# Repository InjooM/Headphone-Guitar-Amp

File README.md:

# Headphone-Guitar-Amp
## Preface
Electric guitar amplifier
I've been meaning to work on my Github more, and I thought this personal project would be the perfect addition to my portfolio. I found a schematic online for a Class AB audio amplifier, and I'm trying my best to follow a procedure where I can ensure the ability to diagnose and treat each and every problem that occurs within my design.

## Finding the circuit
First, I found an [amplifier circuit](http://www.generalguitargadgets.com/pdf/ggg_mxr_hpamp_sc.pdf), and drew it out to help me understand and analyze it. Then I simulated it in Multisim to confirm my calculations. I've included the simulation files in this project.

## Prototyping
I ordered parts and assembled everything onto a protoboard. The amplifier worked properly. I've worked on projects in the past where I'd skip this step, in faith of the circuit I found working out-of-the-box. However, I think this is bad practice, and this step is a good redudancy in case something needs to be tweaked before a board is designed.
Here are some pictures I took of the breadboard. 

## Designing the board
I found footprints off of Mouser for the parts I ordered, then created a schematic in Eagle. After running an ERC, and manually double checking each section of the circuit, I moved over to the board. The board design was quite simple. I tried to keep all capacitors close to I/O, and managed to squeeze all the components into a 40 mm x 70 mm board. I ordered 3 copies of this board from OshPark. I've included the board's files in this project.

## Designing the case
I've worked with Autodesk Fusion and Inventor so I decided to make a casing for this project too. Nothing too special: just a box with faces I can glue together. After a few iterations, it came out fine. I used a friends Creality CR-10 to print. A few issues I ran into were small things: forgetting to add indents to mount connectors and a few errors with Creality's splicer. This cost me some time, and I really should slow down when working on prints. I tend to look over these small mistakes, and it ends up wasting some material. Looking back, I would've also like to add a hinge somewhere inside the top lid to keep things accessible, but besides that the case does the job well. All the dimensions came out correctly, and everything fit within a millimeter or two. I've included the STL's in this project.

## Assembly
Finally, after the boards and parts came in and the prints were finished, I assembled everything. I was nervous about this part, since I didn't have a testbench at home to debug the board if anything went wrong. I only had a multimeter, and I was prepared to use the probes on the via's of the board in case something was wrong. Thankfully, everything worked as soon as it all came together. It sounds better than when I was prototyping it, perhaps due to capcitance in the breadboard? It has a very-small form factor, fits in my palm, and I'm happy about how it turned out.
Here are some screenshots of the finished product.

## Final Thoughts
I initially started this project to save some money on an amp, and to keep my hands busy. If I were to go back and restart the project, I'd definitely make a few changes. For one, I'd find a little more developed circuit, or perhaps a better quality op-amp. I'm not well-versed in the market of op-amps, but I'm sure if I used something better than a general 741, I would get a little less noise from the amp. I also wouldn't have used EAGLE. EAGLE's package system is useful when working on large organized projects, but for something as small as this board, I probably could've used gEDA PCB and spent less time downloading or designing footprints for each component. I also would've chose JLC PCB instead of OSHPark, since although OSHPark makes great boards, it was a lot more expensive. For the casing, I would've wanted the hinge like I mentioned in the above section, and maybe standoffs for the board. As of now, it's just glued to the base plastic piece, which is a little lackluster, and potentially could cause some problems if the plastic or glue ends up being conductive. I also would've liked smoother edges on the casing. The corners are a little sharp.

Otherwise, I'm proud of how this turned out. This was a small pet project I wanted to do on the side to keep me busy while I'm taking classes. I got to use techniques I've learned in school that I haven't used yet for other projects, which was really fun. Analyzing my circuit using the methods I've learned in classes, and seeing it work as I thought in Multisim was very cool. I'm already thinking of new iterations with wireless functionality, so maybe a bluetooth device/interface will be my next project.

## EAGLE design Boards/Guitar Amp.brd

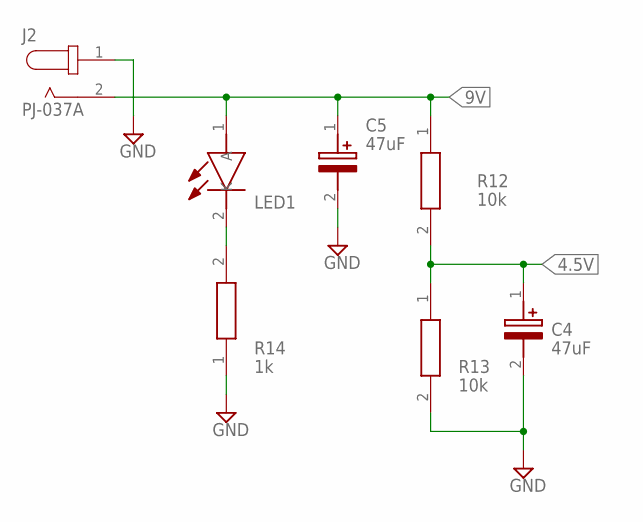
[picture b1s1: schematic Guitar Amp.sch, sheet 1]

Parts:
C4, C5: 47uF; CAPPRD200W55D500H1200
J2: PJ-037A; CUI_PJ-037A
LED1: TLHR4400-AS12Z; TLHR4400AS12Z
R12, R13: 10k; RESAD1630W60L710D230
R14: 1k; RESAD1630W60L710D230

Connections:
4.5V: C4.1 (+), R12.2, R13.1; also elsewhere on the board
9V: C5.1 (+), J2.2, LED1.1 (A), R12.1; also elsewhere on the board
GND: C4.2 (-), C5.2 (-), J2.1, R13.2, R14.1; also elsewhere on the board
unnamed: LED1.2 (K), R14.2

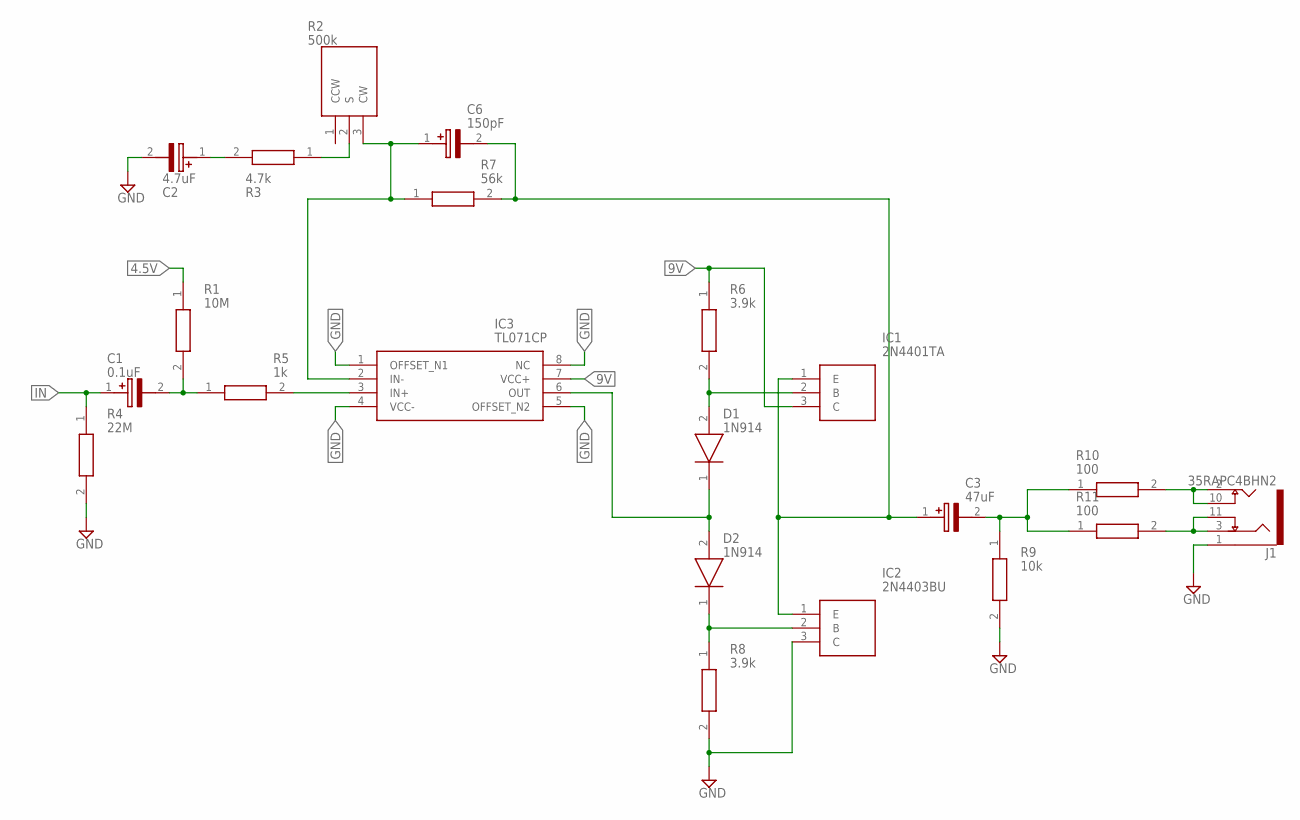
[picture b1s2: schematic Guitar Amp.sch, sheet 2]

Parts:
C1: 0.1uF; CAPPRD200W55D500H1200
C2: 4.7uF; CAPPRD200W55D500H1200
C3: 47uF; CAPPRD200W55D500H1200
C6: 150pF; CAPPRD200W55D500H1200
D1, D2: 1N914; DIO_1N914
IC1: 2N4401TA; KA431AZTA
IC2: 2N4403BU; KA431AZTA
IC3: TL071CP; DIP794W53P254L959H508Q8N
J1: 35RAPC4BHN2; SWITCHCRAFT_35RAPC4BHN2
R1: 10M; RESAD1630W60L710D230
R2: 500k; P160KN0QD15B1MEG
R3: 4.7k; RESAD1630W60L710D230
R4: 22M; RESAD1630W60L710D230
R5: 1k; RESAD1630W60L710D230
R6, R8: 3.9k; RESAD1630W60L710D230
R7: 56k; RESAD1630W60L710D230
R9: 10k; RESAD1630W60L710D230
R10, R11: 100; RESAD1630W60L710D230

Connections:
4.5V: R1.1; also elsewhere on the board
9V: IC1.3 (C), IC3.7 (VCC+), R6.1; also elsewhere on the board
GND: C2.2 (-), IC2.3 (C), IC3.1 (OFFSET_N1), IC3.4 (VCC-), IC3.5 (OFFSET_N2), IC3.8 (NC), J1.1, R4.2, R8.2, R9.2; also elsewhere on the board
IN: C1.1 (+), R4.1
unnamed: C6.1 (+), IC3.2 (IN-), R2.3 (CW), R7.1
unnamed: C1.2 (-), R1.2, R5.1
unnamed: IC3.3 (IN+), R5.2
unnamed: R2.2 (S), R3.1
unnamed: C2.1 (+), R3.2
unnamed: D1.1 (K), D2.2 (A), IC3.6 (OUT)
unnamed: D1.2 (A), IC1.2 (B), R6.2
unnamed: D2.1 (K), IC2.2 (B), R8.1
unnamed: C3.1 (+), C6.2 (-), IC1.1 (E), IC2.1 (E), R7.2
unnamed: C3.2 (-), R9.1, R10.1, R11.1
unnamed: J1.2, J1.10, R10.2
unnamed: J1.3, J1.11, R11.2

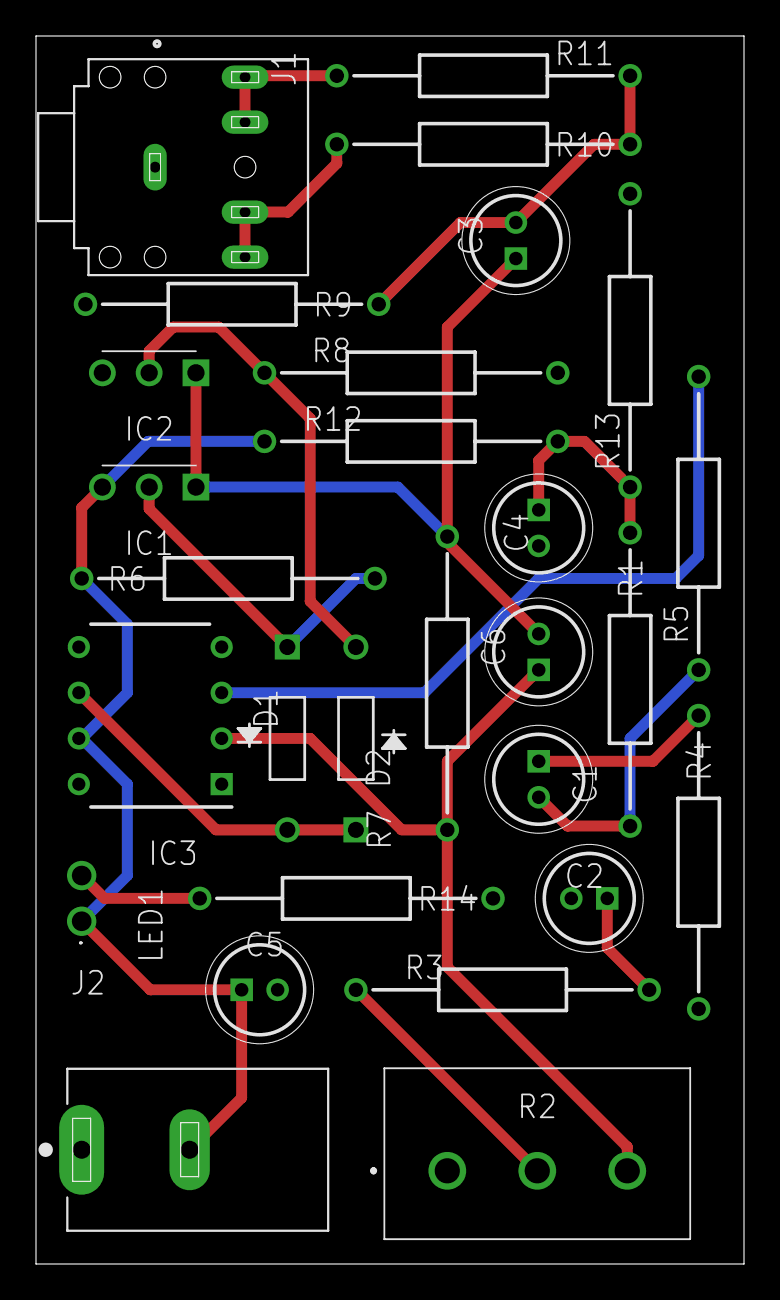
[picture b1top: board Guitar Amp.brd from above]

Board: 2 copper layers, 39.3 x 68.2 mm, 28 parts (0 on the bottom side), 17 nets.

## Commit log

2020-10-12 Create test
2020-10-12 Rename Guitar Amp.brd to Boards/Guitar Amp.brd
2020-10-12 Rename Guitar Amp.sch to Boards/Guitar Amp.sch
